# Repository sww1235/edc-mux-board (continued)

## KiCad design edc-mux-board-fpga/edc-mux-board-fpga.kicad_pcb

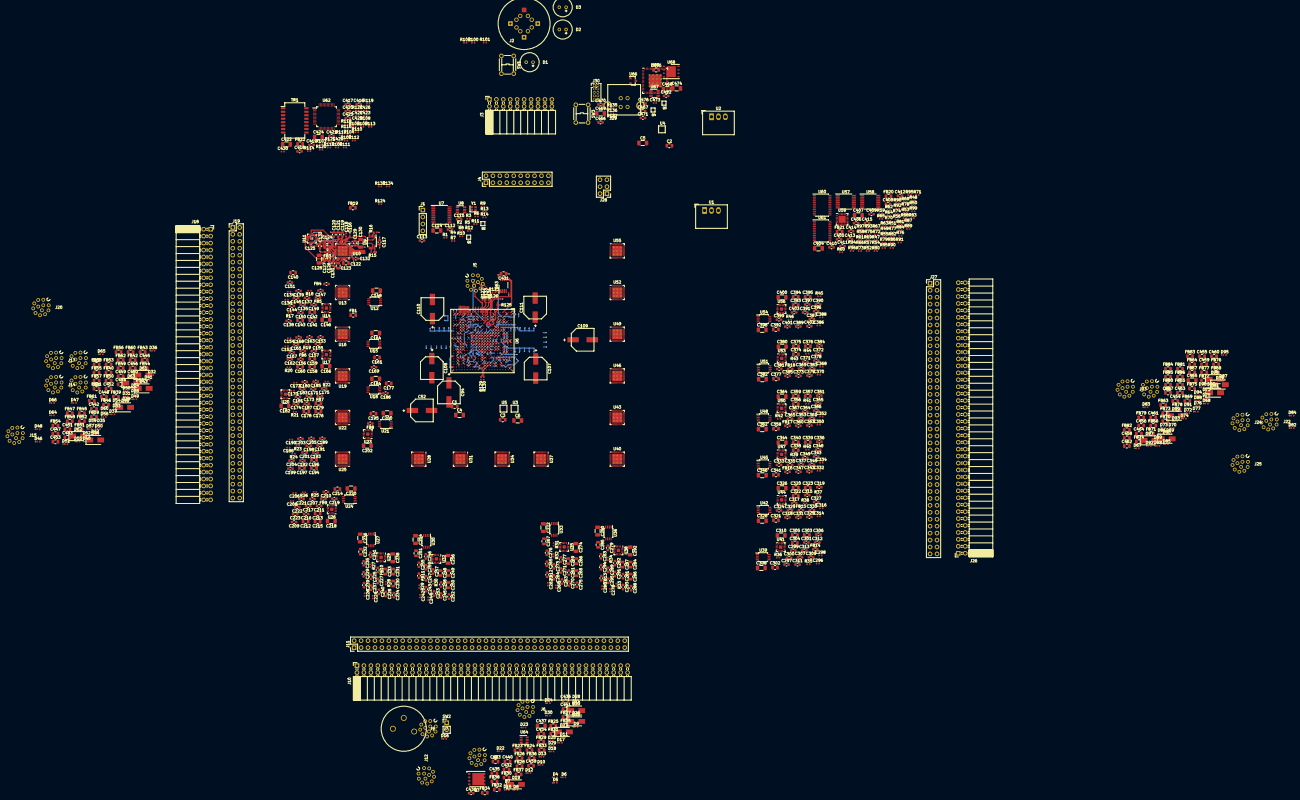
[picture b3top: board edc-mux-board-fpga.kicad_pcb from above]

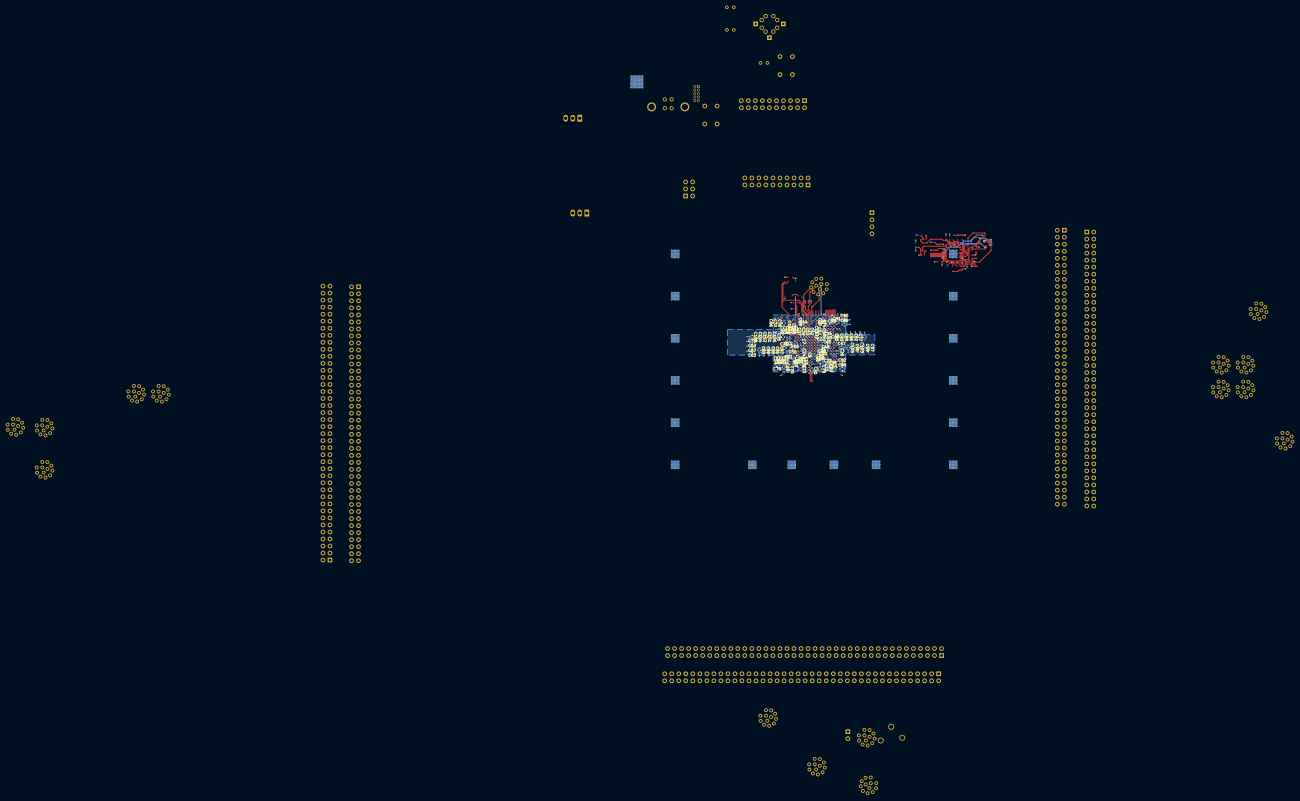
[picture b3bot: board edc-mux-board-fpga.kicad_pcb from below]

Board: 4 copper layers, 906 parts (100 on the bottom side), 887 nets.

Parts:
C1, C2, C3: 4.7uF X7R; C_0805_2012Metric
C4, C5, C6, C114, C128, C130, C146, C148, C164, C166, C182, C184, C200, C202, C218, C220, C236, C238, C254, C256, C272, C274, C290, C292, C308, C310, C326, C328, C344, C346, C362, C364, C380, C382, C398, C400, C404, C407, C422, C424, C437, C465, C468, C469, C474: 10uF X7R; C_1206_3216Metric
C7, C8, C9, C10, C11, C12, C13, C14, C15, C16, C17, C18, C19, C20, C21, C22, C23, C24, C25, C27, C28, C30, C31, C33, C36, C423, C430: 4.7nF X7R; C_0402_1005Metric
C26, C29, C32, C35, C38, C40, C43, C46, C49, C51, C54, C56, C58, C59, C61, C426: 10nF X7R; C_0402_1005Metric
C34, C37, C39, C42, C45, C48, C50, C53, C55, C57: 47nF X7R; C_0603_1608Metric
C41, C44, C60, C62, C63, C64, C65, C66, C67, C68, C69, C70, C71, C72, C73, C74, C75, C76, C77, C78, C79, C81, C112, C113, C115, C117, C119, C120, C126, C129, C131, C132, C133, C135, C137, C138, C144, C147, C149, C150, C151, C153, C155, C156, C162, C165, C167, C168, C169, C171, C173, C174, C180, C183, C185, C186, C187, C189, C191, C192, C198, C201, C203, C204, C205, C207, C209, C210, C216, C219, C221, C222, C223, C225, C227, C228, C234, C237, C239, C240, C241, C243, C245, C246, C252, C255, C257, C258, C259, C261, C263, C264, C270, C273, C275, C276, C277, C279, C281, C282, C288, C291, C293, C294, C295, C297, C299, C300, C306, C309, C311, C312, C313, C315, C317, C318, C324, C327, C329, C330, C331, C333, C335, C336, C342, C345, C347, C348, C349, C351, C353, C354, C360, C363, C365, C366, C367, C369, C371, C372, C378, C381, C383, C384, C385, C387, C389, C390, C396, C399, C401, C402, C403, C406, C409, C411, C413, C415, C416, C417, C418, C419, C420, C421, C425, C466, C470, C471, C476: 100nF X7R; C_0603_1608Metric
C47, C84, C86, C88, C90, C92, C97, C98, C99, C100, C101, C102, C103, C104, C105, C106, C121, C127, C139, C145, C157, C163, C175, C181, C193, C199, C211, C217, C229, C235, C247, C253, C265, C271, C283, C289, C301, C307, C319, C325, C337, C343, C355, C361, C373, C379, C391, C397, C405, C408, C410, C412, C414, C467, C472: 1uF X7R; C_0603_1608Metric
C52, C94, C107, C108, C109, C110, C111: 47uF; CP_ELEC_8.3x8.3x11.7mm_SMD
C80, C82, C83, C85, C87, C89, C91, C93, C95, C96, C438: 220nF X7R; C_0603_1608Metric
C116, C118, C134, C136, C152, C154, C170, C172, C188, C190, C206, C208, C224, C226, C242, C244, C260, C262, C278, C280, C296, C298, C314, C316, C332, C334, C350, C352, C368, C370, C386, C388: 33pF NP0; C_0402_1005Metric
C122, C123, C140, C141, C158, C159, C176, C177, C194, C195, C212, C213, C230, C231, C248, C249, C266, C267, C284, C285, C302, C303, C320, C321, C338, C339, C356, C357, C374, C375, C392, C393, C475: 2.2uF X7R; C_0805_2012Metric
C124, C125, C142, C143, C160, C161, C178, C179, C196, C197, C214, C215, C232, C233, C250, C251, C268, C269, C286, C287, C304, C305, C322, C323, C340, C341, C358, C359, C376, C377, C394, C395, C431, C432, C433, C434, C435, C436, C439, C440, C441, C442, C443, C444, C445, C446, C447, C448, C449, C450, C451, C452, C453, C454, C455, C456, C457, C458, C459, C460, C461, C462, C463, C464: 1uF X7R flex; C_0805_2012Metric
C427, C428: 6.8nF X7R; C_0402_1005Metric
C429: 22nF X7R; C_0402_1005Metric
C473: 100pF C0G; C_0402_1005Metric
D1: LNK_GRN; Q6-pins-epoxy
D2: PWR_RED; Q6-pins-epoxy
D3: ACT_YLW; Q6-pins-epoxy
D4, D5, D6, D7, D8, D9, D10, D11, D12, D13, D14, D15, D16, D17, D18, D22, D23, D24, D25, D26, D28, D29, D30, D31, D32, D33, D34, D35, D36, D37, D38, D39, D40, D41, D42, D46, D47, D48, D49, D50, D51, D52, D53, D54, D55, D56, D57, D58, D59, D60, D64, D65, D66, D67, D68, D69, D70, D71, D72, D73, D74, D75, D76, D77, D78, D82, D83, D84, D85, D86, D87, D88, D89, D90, D91, D92, D93, D94, D95, D96: 30pF 30kV; D_0402_1005Metric
D19, D20, D21, D27, D43, D44, D45, D61, D62, D63, D79, D80, D81, D97, D98, D99: 12V_Vrso; D_SMA
FB1, FB2, FB19, FB20, FB21, FB22, FB23, FB24, FB25, FB26, FB27, FB28, FB29, FB30, FB31, FB32, FB33, FB34, FB35, FB36, FB37, FB38, FB39, FB40, FB41, FB42, FB43, FB44, FB45, FB46, FB47, FB48, FB49, FB50, FB51, FB52, FB53, FB54, FB55, FB56, FB57, FB58, FB59, FB60, FB61, FB62, FB63, FB64, FB65, FB66, FB67, FB68, FB69, FB70, FB71, FB72, FB73, FB74, FB75, FB76, FB77, FB78, FB79, FB80, FB81, FB82, FB83, FB84, FB85, FB86: 600Ω @ 100MHz; L_0805_2012Metric
FB3, FB4, FB5, FB6, FB7, FB8, FB9, FB10, FB11, FB12, FB13, FB14, FB15, FB16, FB17, FB18: 220Ω/2A; L_0603_1608Metric
J1: OSC_PRG_HDR; PinHeader_1x04_P2.54mm_Vertical
J2: Ethernet; 43-02758
J3: Left Mezzanine Board Connector (Daughterboard); PinSocket_2x10_P2.54mm_Horizontal
J4: Left Mezzanine Board Connector (Motherboard); PinHeader_2x10_P2.54mm_Vertical
J5: Device 6; T4141012121-000
J6: Device 7; T4141012121-000
J7: Device 8; T4141012121-000
J8: Device 9; T4141012121-000
J9: Power In; PCL712AS
J10, J18, J26: Left Mezzanine Board Connector (Daughterboard); PinSocket_2x40_P2.54mm_Horizontal
J11, J19, J27: Left Mezzanine Board Connector (Motherboard); PinHeader_2x40_P2.54mm_Vertical
J12: Device 0; T4141012121-000
J13: Device 1; T4141012121-000
J14: Device 2; T4141012121-000
J15: Device 3; T4141012121-000
J16: Device 4; T4141012121-000
J17: Device 5; T4141012121-000
J20: Device 10; T4141012121-000
J21: Device 11; T4141012121-000
J22: Device 12; T4141012121-000
J23: Device 13; T4141012121-000
J24: Device 14; T4141012121-000
J25: Device 15; T4141012121-000
J28: PRG/SWD; PinHeader_2x03_P2.54mm_Vertical
J29: USB PRG; UJ2-BV-1-TH
J30: FPGA_JTAG; PinHeader_2x05_P1.27mm_Vertical
Q1, Q2, Q4, Q5: CSD22206W; DSBGA9
Q3: CSD18501Q5A; TDSON-8-1
R1, R3, R4, R5, R125, R132: 1kΩ; R_0402_1005Metric
R2, R104, R105, R106, R107: 0Ω; R_0402_1005Metric
R6, R7, R47, R48, R65, R66, R67, R68, R69, R70, R71, R72, R73, R74, R75, R76, R77, R78, R79, R80, R81, R82, R83, R84, R85, R86, R87, R88, R89, R90, R91, R92, R93, R94, R95, R96, R97, R98, R99, R123, R124, R130, R131, R133, R134, R135, R136, R137: 10kΩ; R_0402_1005Metric
R8, R128: 470kΩ; R_0402_1005Metric
R9, R10, R11, R12, R13, R14, R49, R50, R51, R52, R53, R54, R55, R56, R57, R58, R59, R60, R61, R62, R63, R64: 5Ω; R_0402_1005Metric
R15, R16, R17, R18, R19, R20, R21, R22, R23, R24, R25, R26, R27, R28, R29, R30, R31, R32, R33, R34, R35, R36, R37, R38, R39, R40, R41, R42, R43, R44, R45, R46: 750Ω; R_0402_1005Metric
R100, R101, R102, R127: 330Ω; R_0402_1005Metric
R103: 12.4Ω 1%; R_0402_1005Metric
R108, R110: 82Ω 1%; R_0402_1005Metric
R109, R111, R117, R118, R119, R120, R121, R122: 49.9Ω 1%; R_0402_1005Metric
R112: 10Ω 1%; R_0402_1005Metric
R113, R114: 75Ω 1%; R_0402_1005Metric
R115, R116: 150Ω 1%; R_0402_1005Metric
R126: 2k2Ω; R_0402_1005Metric
R129: 25Ω; R_0402_1005Metric
SW1: LED_ENABLE; TL1105
SW2: Power Switch; PinHeader_1x02_P2.54mm_Vertical
SW3: Reset (Microprocessor); TL1105
TR1: H1102NL; Transformer_Pulse_H1100NL
U1: R-78B12-2.0; Converter_DCDC_RECOM_R-78B-2.0_THT
U2: R-78B3.3-2.0; Converter_DCDC_RECOM_R-78B-2.0_THT
U3, U4: EP5358HUI; ENPIRION_QFN16_2.5x2.25x1.1mm-0.4mm
U5: EP5358LUI; ENPIRION_QFN16_2.5x2.25x1.1mm-0.4mm
U6: 10CL040YF484I7G; FBGA-484_23.0x23.0mm_Layout22x22_P1.0mm
U7: CDCE706; TSSOP-20_4.4x6.5mm_P0.65mm
U8, U67: LTC4412; TSOT-23-6
U9, U12, U15, U18, U21, U24, U27, U30, U33, U36, U39, U42, U45, U48, U51, U54: P82B96; TSSOP-8_3x3mm_P0.65mm
U10, U13, U16, U19, U22, U25, U28, U31, U34, U37, U40, U43, U46, U49, U52, U55: TLV320AIC3206; UQFN-40-1EP_5x5mm_P0.4mm_EP3.8x3.8mm_ThermalVias
U11, U14, U17, U20, U23, U26, U29, U32, U35, U38, U41, U44, U47, U50, U53, U56: MAX4910; TQFN-16-1EP_3x3mm_P0.5mm_EP1.23x1.23mm
U57, U58: CDCLVC1108; TSSOP-16_4.4x5mm_P0.65mm
U59: TCA9555RTWR; QFN-24-1EP_4x4mm_P0.5mm_EP2.6x2.6mm
U60, U61: TCA9548A; TSSOP-24_4.4x7.8mm_P0.65mm
U62: W5500; TQFP-48_7x7mm_P0.5mm
U63: LM74610-Q1; VSSOP-8_3.0x3.0mm_P0.65mm
U64: TPD3S014; SOT-23-6
U65: SAMD21JXXAM; QFN-64-1EP_9x9mm_P0.5mm_EP4.7x4.7mm_ThermalVias
U66: MCP1812; SOT-23
U68: S25FL128L; WSON-8-1EP_6x5mm_P1.27mm_EP3.4x4mm
Y1: SiT1602BI-71-33E-48.000000; Crystal_SMD_2016-4Pin_2.0x1.6mm

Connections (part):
+1V2: C6.1, C7.1, C8.1, C9.1, C12.1, C15.1, C18.1, C21.1, C24.1, C27.1, C30.1, C34.1, C37.1, C39.1, C42.1, C45.1, C48.1, C50.1, C53.1, C55.1, C57.1, C60.1, C62.1, C63.1, C65.1, C67.1, C69.1, C71.1, C73.1, C75.1, C77.1, C80.1, C82.1, C83.1, C85.1, C87.1, C89.1, C91.1, C93.1, C95.1, C96.1, C97.1, C98.1, C99.1, C100.1, C101.1, C102.1, C103.1, C104.1, C105.1, C106.1, C107.1, C108.1, C109.1, C110.1, C111.1, FB1.1, U5.5, U5.7, U5.8, U6.G12, U6.H9, U6.J10, U6.J11, U6.J12, U6.J13, U6.J14, U6.J16, U6.K9, U6.K14, U6.K15, U6.L9, U6.L14, U6.L16, U6.M9, U6.M14, U6.M15, U6.N9, U6.N14, U6.P9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
+1V8: C5.1, C126.2, C127.2, C128.2, C131.2, C132.2, C144.2, C145.2, C146.2, C149.2, C150.2, C162.2, C163.2, C164.2, C167.2, C168.2, C180.2, C181.2, C182.2, C185.2, C186.2, C198.2, C199.2, C200.2, C203.2, C204.2, C216.2, C217.2, C218.2, C221.2, C222.2, C234.2, C235.2, C236.2, C239.2, C240.2, C252.2, C253.2, C254.2, C257.2, C258.2, C270.2, C271.2, C272.2, C275.2, C276.2, C288.2, C289.2, C290.2, C293.2, C294.2, C306.2, C307.2, C308.2, C311.2, C312.2, C324.2, C325.2, C326.2, C329.2, C330.2, C342.2, C343.2, C344.2, C347.2, C348.2, C360.2, C361.2, C362.2, C365.2, C366.2, C378.2, C379.2, C380.2, C383.2, C384.2, C396.2, C397.2, C398.2, C401.2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
+2V5: C4.1, C10.1, C13.1, C16.1, C19.1, C22.1, C25.1, C28.1, C31.1, C33.1, C36.1, C40.1, C43.1, C46.1, C49.1, C51.1, C54.1, C56.1, C58.1, C59.1, C61.1, C64.1, C66.1, C68.1, C70.1, C72.1, C74.1, C76.1, C78.1, C79.1, C81.1, C84.1, C86.1, C88.1, C90.1, C92.1, C94.1, J30.9, R136.2, R137.2, U3.5, U3.7, U3.8, U6.F18, U6.G6, U6.T6, U6.U18
+3V3: C1.1, C2.1, C3.1, C11.1, C14.1, C17.1, C20.1, C23.1, C26.1, C29.1, C32.1, C35.1, C38.1, C41.1, C44.1, C47.1, C52.1, C129.2, C130.1, C133.2, C147.2, C148.1, C151.2, C165.2, C166.1, C169.2, C183.2, C184.1, C187.2, C201.2, C202.1, C205.2, C219.2, C220.1, C223.2, C237.2, C238.1, C241.2, C255.2, C256.1, C259.2, C273.2, C274.1, C277.2, C291.2, C292.1, C295.2, C309.2, C310.1, C313.2, C327.2, C328.1, C331.2, C345.2, C346.1, C349.2, C363.2, C364.1, C367.2, C381.2, C382.1, C385.2, C399.2, C400.1, C403.2, C404.1, C407.1, C410.1, C411.2, C412.1, C413.2, C414.1, C415.2, C424.2, C425.2, C473.2, C476.2, FB19.2, FB20.2, FB21.2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
+12P: J11.27, J11.28, J11.29, J11.30, J11.31, J11.32, J11.49, J11.50, J11.51, J11.52, J11.53, J11.54, U1.1
+12V: C117.1, C135.1, C153.1, C171.1, C189.1, C207.1, C225.1, C243.1, C261.1, C279.1, C297.1, C315.1, C333.1, C351.1, C369.1, C387.1, J11.37, J11.38, J11.39, J11.40, J11.41, J11.42, J11.43, J11.44, J19.37, J19.38, J19.39, J19.40, J19.41, J19.42, J19.43, J19.44, J27.37, J27.38, J27.39, J27.40, J27.41, J27.42, J27.43, J27.44, R15.1, R16.1, R17.1, R18.1, R19.1, R20.1, R21.1, R22.1, R23.1, R24.1, R25.1, R26.1, R27.1, R28.1, R29.1, R30.1, R31.1, R32.1, R33.1, R34.1, R35.1, R36.1, R37.1, R38.1, R39.1, R40.1, R41.1, R42.1, R43.1, R44.1, R45.1, R46.1, U1.3, U2.1, U9.8, U12.8, U15.8, U18.8, U21.8, U24.8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
/ATTACH_INT: U6.R1, U65.40
/Bottom Side Daughterboard Connector Interconnects/AUD_GND6: J11.5, U29.4
/Bottom Side Daughterboard Connector Interconnects/AUD_GND7: J11.17, U32.4
/Bottom Side Daughterboard Connector Interconnects/AUD_GND8: J11.63, U35.4
/Bottom Side Daughterboard Connector Interconnects/AUD_GND9: J11.75, U38.4
/Bottom Side Daughterboard Connector Interconnects/L_IN6: C224.2, J11.3, U28.17
/Bottom Side Daughterboard Connector Interconnects/L_IN7: C242.2, J11.15, U31.17
/Bottom Side Daughterboard Connector Interconnects/L_IN8: C260.2, J11.61, U34.17
/Bottom Side Daughterboard Connector Interconnects/L_IN9: C278.2, J11.73, U37.17
/Bottom Side Daughterboard Connector Interconnects/L_OUT6: J11.4, U29.8
/Bottom Side Daughterboard Connector Interconnects/L_OUT7: J11.16, U32.8
/Bottom Side Daughterboard Connector Interconnects/L_OUT8: J11.62, U35.8
/Bottom Side Daughterboard Connector Interconnects/L_OUT9: J11.74, U38.8
/Bottom Side Daughterboard Connector Interconnects/M_+12V: D19.1, D20.1, D21.1, D27.1, J5.12, J6.12, J7.12, J8.12, J10.37, J10.38, J10.39, J10.40, J10.41, J10.42, J10.43, J10.44
/Bottom Side Daughterboard Connector Interconnects/M_AUD_GND6: J5.1, J10.5
/Bottom Side Daughterboard Connector Interconnects/M_AUD_GND7: J6.1, J10.17
/Bottom Side Daughterboard Connector Interconnects/M_AUD_GND8: J7.1, J10.63
/Bottom Side Daughterboard Connector Interconnects/M_AUD_GND9: J8.1, J10.75
/Bottom Side Daughterboard Connector Interconnects/M_GND: C437.1, D4.2, D5.2, D6.2, D7.2, D8.2, D9.2, D10.2, D11.2, D12.2, D13.2, D14.2, D15.2, D16.2, D17.2, D18.2, D19.2, D20.2, D21.2, D22.2, D23.2, D24.2, D25.2, D26.2, D27.2, J5.6, J5.10, J6.6, J6.10, J7.6, J7.10, J8.6, J8.10, J9.2, J9.3, J10.6, J10.11, J10.12, J10.18, J10.23, J10.24, J10.25, J10.26, J10.33, J10.34, J10.35, J10.36, J10.45, J10.46, J10.47, J10.48, J10.55, J10.56, J10.57, J10.58, J10.64, J10.69, J10.70, J10.76
/Bottom Side Daughterboard Connector Interconnects/M_ID_PIN6: D16.1, J5.11, J10.9
/Bottom Side Daughterboard Connector Interconnects/M_ID_PIN7: D17.1, J6.11, J10.21
/Bottom Side Daughterboard Connector Interconnects/M_ID_PIN8: D18.1, J7.11, J10.67
/Bottom Side Daughterboard Connector Interconnects/M_ID_PIN9: D26.1, J8.11, J10.79
/Bottom Side Daughterboard Connector Interconnects/M_INT_6: J5.9, J10.7
/Bottom Side Daughterboard Connector Interconnects/M_INT_7: J6.9, J10.19
/Bottom Side Daughterboard Connector Interconnects/M_INT_8: J7.9, J10.65
/Bottom Side Daughterboard Connector Interconnects/M_INT_9: J8.9, J10.77
/Bottom Side Daughterboard Connector Interconnects/M_L_IN6: C431.1, J10.3
/Bottom Side Daughterboard Connector Interconnects/M_L_IN7: C432.1, J10.15
/Bottom Side Daughterboard Connector Interconnects/M_L_IN8: C433.1, J10.61
/Bottom Side Daughterboard Connector Interconnects/M_L_IN9: C439.1, J10.73
/Bottom Side Daughterboard Connector Interconnects/M_L_OUT6: FB28.1, J10.2
/Bottom Side Daughterboard Connector Interconnects/M_L_OUT7: FB29.1, J10.16
/Bottom Side Daughterboard Connector Interconnects/M_L_OUT8: FB30.1, J10.62
/Bottom Side Daughterboard Connector Interconnects/M_L_OUT9: FB36.1, J10.74
/Bottom Side Daughterboard Connector Interconnects/M_PWR_IN: J10.27, J10.28, J10.29, J10.30, J10.31, J10.32, J10.49, J10.50, J10.51, J10.52, J10.53, J10.54, Q3.5, U63.8
/Bottom Side Daughterboard Connector Interconnects/M_R_IN6: C434.1, J10.1
/Bottom Side Daughterboard Connector Interconnects/M_R_IN7: C435.1, J10.13
/Bottom Side Daughterboard Connector Interconnects/M_R_IN8: C436.1, J10.59
/Bottom Side Daughterboard Connector Interconnects/M_R_IN9: C440.1, J10.71
/Bottom Side Daughterboard Connector Interconnects/M_R_OUT6: FB31.1, J10.4
/Bottom Side Daughterboard Connector Interconnects/M_R_OUT7: FB32.1, J10.14
/Bottom Side Daughterboard Connector Interconnects/M_R_OUT8: FB33.1, J10.60
/Bottom Side Daughterboard Connector Interconnects/M_R_OUT9: FB37.1, J10.72
/Bottom Side Daughterboard Connector Interconnects/M_SCL_HV6: J5.8, J10.8
/Bottom Side Daughterboard Connector Interconnects/M_SCL_HV7: J6.8, J10.20
/Bottom Side Daughterboard Connector Interconnects/M_SCL_HV8: J7.8, J10.66
/Bottom Side Daughterboard Connector Interconnects/M_SCL_HV9: J8.8, J10.78
/Bottom Side Daughterboard Connector Interconnects/M_SDA_HV6: J5.7, J10.10
/Bottom Side Daughterboard Connector Interconnects/M_SDA_HV7: J6.7, J10.22
/Bottom Side Daughterboard Connector Interconnects/M_SDA_HV8: J7.7, J10.68
/Bottom Side Daughterboard Connector Interconnects/M_SDA_HV9: J8.7, J10.80
/Bottom Side Daughterboard Connector Interconnects/R_IN6: C226.2, J11.1, U28.18
/Bottom Side Daughterboard Connector Interconnects/R_IN7: C244.2, J11.13, U31.18
/Bottom Side Daughterboard Connector Interconnects/R_IN8: C262.2, J11.59, U34.18
/Bottom Side Daughterboard Connector Interconnects/R_IN9: C280.2, J11.71, U37.18
/Bottom Side Daughterboard Connector Interconnects/SCL_HV6: J11.8, R27.2, U27.5, U27.6
/Bottom Side Daughterboard Connector Interconnects/SCL_HV7: J11.20, R29.2, U30.5, U30.6
/Bottom Side Daughterboard Connector Interconnects/SCL_HV8: J11.66, R31.2, U33.5, U33.6
/Bottom Side Daughterboard Connector Interconnects/SCL_HV9: J11.78, R33.2, U36.5, U36.6
/Bottom Side Daughterboard Connector Interconnects/SDA_HV6: J11.10, R28.2, U27.2, U27.3
/Bottom Side Daughterboard Connector Interconnects/SDA_HV7: J11.22, R30.2, U30.2, U30.3
/Bottom Side Daughterboard Connector Interconnects/SDA_HV8: J11.68, R32.2, U33.2, U33.3
/Bottom Side Daughterboard Connector Interconnects/SDA_HV9: J11.80, R34.2, U36.2, U36.3
/CODEC interconnection sheet/AUD_GND0: J19.5, U11.4
/CODEC interconnection sheet/AUD_GND1: J19.17, U14.4
/CODEC interconnection sheet/AUD_GND2: J19.29, U17.4
/CODEC interconnection sheet/AUD_GND3: J19.51, U20.4
/CODEC interconnection sheet/AUD_GND4: J19.63, U23.4
/CODEC interconnection sheet/AUD_GND5: J19.75, U26.4
/CODEC interconnection sheet/AUD_GND10: J27.5, U41.4
/CODEC interconnection sheet/AUD_GND11: J27.17, U44.4
/CODEC interconnection sheet/AUD_GND12: J27.29, U47.4
/CODEC interconnection sheet/AUD_GND13: J27.51, U50.4
/CODEC interconnection sheet/AUD_GND14: J27.63, U53.4
/CODEC interconnection sheet/AUD_GND15: J27.75, U56.4
/CODEC interconnection sheet/BCLK0: U6.AA4, U10.6
/CODEC interconnection sheet/BCLK1: U6.AA8, U13.6
/CODEC interconnection sheet/BCLK2: U6.AA10, U16.6
/CODEC interconnection sheet/BCLK3: U6.AA14, U19.6
/CODEC interconnection sheet/BCLK4: U6.AA16, U22.6
/CODEC interconnection sheet/BCLK5: U6.AA19, U25.6
/CODEC interconnection sheet/BCLK6: U6.Y21, U28.6
/CODEC interconnection sheet/BCLK7: U6.U21, U31.6
/CODEC interconnection sheet/BCLK8: U6.G21, U34.6
/CODEC interconnection sheet/BCLK9: U6.D21, U37.6
/CODEC interconnection sheet/BCLK10: U6.B15, U40.6
/CODEC interconnection sheet/BCLK11: U6.B13, U43.6
/CODEC interconnection sheet/BCLK12: U6.B9, U46.6
/CODEC interconnection sheet/BCLK13: U6.B7, U49.6
/CODEC interconnection sheet/BCLK14: U6.B5, U52.6
/CODEC interconnection sheet/BCLK15: U6.B3, U55.6
/CODEC interconnection sheet/DIN0: U6.AA3, U10.8
/CODEC interconnection sheet/DIN1: U6.AA7, U13.8
/CODEC interconnection sheet/DIN2: U6.AA9, U16.8
/CODEC interconnection sheet/DIN3: U6.AA13, U19.8
/CODEC interconnection sheet/DIN4: U6.AA15, U22.8
/CODEC interconnection sheet/DIN5: U6.AA18, U25.8
/CODEC interconnection sheet/DIN6: U6.AA21, U28.8
/CODEC interconnection sheet/DIN7: U6.V21, U31.8
/CODEC interconnection sheet/DIN8: U6.H21, U34.8
/CODEC interconnection sheet/DIN9: U6.E21, U37.8
/CODEC interconnection sheet/DIN10: U6.B16, U40.8
/CODEC interconnection sheet/DIN11: U6.B14, U43.8
/CODEC interconnection sheet/DIN12: U6.B10, U46.8
/CODEC interconnection sheet/DIN13: U6.B8, U49.8
/CODEC interconnection sheet/DIN14: U6.B6, U52.8
/CODEC interconnection sheet/DIN15: U6.B4, U55.8
/CODEC interconnection sheet/DOUT0: U6.AB3, U10.9
/CODEC interconnection sheet/DOUT1: U6.AB7, U13.9
/CODEC interconnection sheet/DOUT2: U6.AB9, U16.9
/CODEC interconnection sheet/DOUT3: U6.AB13, U19.9
/CODEC interconnection sheet/DOUT4: U6.AB15, U22.9
/CODEC interconnection sheet/DOUT5: U6.AB18, U25.9
/CODEC interconnection sheet/DOUT6: U6.AA22, U28.9
/CODEC interconnection sheet/DOUT7: U6.V22, U31.9
/CODEC interconnection sheet/DOUT8: U6.H22, U34.9
/CODEC interconnection sheet/DOUT9: U6.E22, U37.9
/CODEC interconnection sheet/DOUT10: U6.A16, U40.9
/CODEC interconnection sheet/DOUT11: U6.A14, U43.9
/CODEC interconnection sheet/DOUT12: U6.A10, U46.9
/CODEC interconnection sheet/DOUT13: U6.A8, U49.9
/CODEC interconnection sheet/DOUT14: U6.A6, U52.9
/CODEC interconnection sheet/DOUT15: U6.A4, U55.9
/CODEC interconnection sheet/Interface - Connector 0/GND_SENSE: FB3.1, U10.28, U11.3
/CODEC interconnection sheet/Interface - Connector 0/HPL: U10.31, U11.15
/CODEC interconnection sheet/Interface - Connector 0/HPR: U10.33, U11.7
/CODEC interconnection sheet/Interface - Connector 0/HP_~LINE~_SEL: U10.4, U11.2, U11.10
/CODEC interconnection sheet/Interface - Connector 0/LINE_OUT_L: C124.1, U11.1
/CODEC interconnection sheet/Interface - Connector 0/LINE_OUT_R: C125.1, U11.9
/CODEC interconnection sheet/Interface - Connector 0/REF: C121.2, U10.22
/CODEC interconnection sheet/Interface - Connector 0/VNEG: C123.2, U10.35
/CODEC interconnection sheet/Interface - Connector 1/GND_SENSE: FB4.1, U13.28, U14.3
/CODEC interconnection sheet/Interface - Connector 1/HPL: U13.31, U14.15
/CODEC interconnection sheet/Interface - Connector 1/HPR: U13.33, U14.7
/CODEC interconnection sheet/Interface - Connector 1/HP_~LINE~_SEL: U13.4, U14.2, U14.10
/CODEC interconnection sheet/Interface - Connector 1/LINE_OUT_L: C142.1, U14.1
/CODEC interconnection sheet/Interface - Connector 1/LINE_OUT_R: C143.1, U14.9
/CODEC interconnection sheet/Interface - Connector 1/REF: C139.2, U13.22
/CODEC interconnection sheet/Interface - Connector 1/VNEG: C141.2, U13.35
/CODEC interconnection sheet/Interface - Connector 2/GND_SENSE: FB5.1, U16.28, U17.3
/CODEC interconnection sheet/Interface - Connector 2/HPL: U16.31, U17.15
/CODEC interconnection sheet/Interface - Connector 2/HPR: U16.33, U17.7
/CODEC interconnection sheet/Interface - Connector 2/HP_~LINE~_SEL: U16.4, U17.2, U17.10
/CODEC interconnection sheet/Interface - Connector 2/LINE_OUT_L: C160.1, U17.1
/CODEC interconnection sheet/Interface - Connector 2/LINE_OUT_R: C161.1, U17.9
/CODEC interconnection sheet/Interface - Connector 2/REF: C157.2, U16.22
/CODEC interconnection sheet/Interface - Connector 2/VNEG: C159.2, U16.35
/CODEC interconnection sheet/Interface - Connector 3/GND_SENSE: FB6.1, U19.28, U20.3
/CODEC interconnection sheet/Interface - Connector 3/HPL: U19.31, U20.15
/CODEC interconnection sheet/Interface - Connector 3/HPR: U19.33, U20.7
/CODEC interconnection sheet/Interface - Connector 3/HP_~LINE~_SEL: U19.4, U20.2, U20.10
/CODEC interconnection sheet/Interface - Connector 3/LINE_OUT_L: C178.1, U20.1
/CODEC interconnection sheet/Interface - Connector 3/LINE_OUT_R: C179.1, U20.9
/CODEC interconnection sheet/Interface - Connector 3/REF: C175.2, U19.22
/CODEC interconnection sheet/Interface - Connector 3/VNEG: C177.2, U19.35
/CODEC interconnection sheet/Interface - Connector 4/GND_SENSE: FB7.1, U22.28, U23.3
/CODEC interconnection sheet/Interface - Connector 4/HPL: U22.31, U23.15
/CODEC interconnection sheet/Interface - Connector 4/HPR: U22.33, U23.7
/CODEC interconnection sheet/Interface - Connector 4/HP_~LINE~_SEL: U22.4, U23.2, U23.10
/CODEC interconnection sheet/Interface - Connector 4/LINE_OUT_L: C196.1, U23.1
/CODEC interconnection sheet/Interface - Connector 4/LINE_OUT_R: C197.1, U23.9
/CODEC interconnection sheet/Interface - Connector 4/REF: C193.2, U22.22
/CODEC interconnection sheet/Interface - Connector 4/VNEG: C195.2, U22.35
/CODEC interconnection sheet/Interface - Connector 5/GND_SENSE: FB8.1, U25.28, U26.3
/CODEC interconnection sheet/Interface - Connector 5/HPL: U25.31, U26.15
/CODEC interconnection sheet/Interface - Connector 5/HPR: U25.33, U26.7
/CODEC interconnection sheet/Interface - Connector 5/HP_~LINE~_SEL: U25.4, U26.2, U26.10
/CODEC interconnection sheet/Interface - Connector 5/LINE_OUT_L: C214.1, U26.1
/CODEC interconnection sheet/Interface - Connector 5/LINE_OUT_R: C215.1, U26.9
/CODEC interconnection sheet/Interface - Connector 5/REF: C211.2, U25.22
/CODEC interconnection sheet/Interface - Connector 5/VNEG: C213.2, U25.35
/CODEC interconnection sheet/Interface - Connector 6/GND_SENSE: FB9.1, U28.28, U29.3
/CODEC interconnection sheet/Interface - Connector 6/HPL: U28.31, U29.15
/CODEC interconnection sheet/Interface - Connector 6/HPR: U28.33, U29.7
/CODEC interconnection sheet/Interface - Connector 6/HP_~LINE~_SEL: U28.4, U29.2, U29.10
/CODEC interconnection sheet/Interface - Connector 6/LINE_OUT_L: C232.1, U29.1
/CODEC interconnection sheet/Interface - Connector 6/LINE_OUT_R: C233.1, U29.9
/CODEC interconnection sheet/Interface - Connector 6/REF: C229.2, U28.22
/CODEC interconnection sheet/Interface - Connector 6/VNEG: C231.2, U28.35
/CODEC interconnection sheet/Interface - Connector 7/GND_SENSE: FB10.1, U31.28, U32.3
/CODEC interconnection sheet/Interface - Connector 7/HPL: U31.31, U32.15
/CODEC interconnection sheet/Interface - Connector 7/HPR: U31.33, U32.7
/CODEC interconnection sheet/Interface - Connector 7/HP_~LINE~_SEL: U31.4, U32.2, U32.10
/CODEC interconnection sheet/Interface - Connector 7/LINE_OUT_L: C250.1, U32.1
/CODEC interconnection sheet/Interface - Connector 7/LINE_OUT_R: C251.1, U32.9
/CODEC interconnection sheet/Interface - Connector 7/REF: C247.2, U31.22
/CODEC interconnection sheet/Interface - Connector 7/VNEG: C249.2, U31.35
/CODEC interconnection sheet/Interface - Connector 8/GND_SENSE: FB11.1, U34.28, U35.3
/CODEC interconnection sheet/Interface - Connector 8/HPL: U34.31, U35.15
/CODEC interconnection sheet/Interface - Connector 8/HPR: U34.33, U35.7
/CODEC interconnection sheet/Interface - Connector 8/HP_~LINE~_SEL: U34.4, U35.2, U35.10
/CODEC interconnection sheet/Interface - Connector 8/LINE_OUT_L: C268.1, U35.1
/CODEC interconnection sheet/Interface - Connector 8/LINE_OUT_R: C269.1, U35.9
/CODEC interconnection sheet/Interface - Connector 8/REF: C265.2, U34.22
/CODEC interconnection sheet/Interface - Connector 8/VNEG: C267.2, U34.35
/CODEC interconnection sheet/Interface - Connector 9/GND_SENSE: FB12.1, U37.28, U38.3
/CODEC interconnection sheet/Interface - Connector 9/HPL: U37.31, U38.15
/CODEC interconnection sheet/Interface - Connector 9/HPR: U37.33, U38.7
/CODEC interconnection sheet/Interface - Connector 9/HP_~LINE~_SEL: U37.4, U38.2, U38.10
/CODEC interconnection sheet/Interface - Connector 9/LINE_OUT_L: C286.1, U38.1
/CODEC interconnection sheet/Interface - Connector 9/LINE_OUT_R: C287.1, U38.9
/CODEC interconnection sheet/Interface - Connector 9/REF: C283.2, U37.22
/CODEC interconnection sheet/Interface - Connector 9/VNEG: C285.2, U37.35
/CODEC interconnection sheet/Interface - Connector 10/GND_SENSE: FB13.1, U40.28, U41.3
/CODEC interconnection sheet/Interface - Connector 10/HPL: U40.31, U41.15
/CODEC interconnection sheet/Interface - Connector 10/HPR: U40.33, U41.7
/CODEC interconnection sheet/Interface - Connector 10/HP_~LINE~_SEL: U40.4, U41.2, U41.10
/CODEC interconnection sheet/Interface - Connector 10/LINE_OUT_L: C304.1, U41.1
/CODEC interconnection sheet/Interface - Connector 10/LINE_OUT_R: C305.1, U41.9
/CODEC interconnection sheet/Interface - Connector 10/REF: C301.2, U40.22
/CODEC interconnection sheet/Interface - Connector 10/VNEG: C303.2, U40.35
/CODEC interconnection sheet/Interface - Connector 11/GND_SENSE: FB14.1, U43.28, U44.3
/CODEC interconnection sheet/Interface - Connector 11/HPL: U43.31, U44.15
/CODEC interconnection sheet/Interface - Connector 11/HPR: U43.33, U44.7
/CODEC interconnection sheet/Interface - Connector 11/HP_~LINE~_SEL: U43.4, U44.2, U44.10
/CODEC interconnection sheet/Interface - Connector 11/LINE_OUT_L: C322.1, U44.1
/CODEC interconnection sheet/Interface - Connector 11/LINE_OUT_R: C323.1, U44.9
/CODEC interconnection sheet/Interface - Connector 11/REF: C319.2, U43.22
/CODEC interconnection sheet/Interface - Connector 11/VNEG: C321.2, U43.35
/CODEC interconnection sheet/Interface - Connector 12/GND_SENSE: FB15.1, U46.28, U47.3
/CODEC interconnection sheet/Interface - Connector 12/HPL: U46.31, U47.15
/CODEC interconnection sheet/Interface - Connector 12/HPR: U46.33, U47.7
/CODEC interconnection sheet/Interface - Connector 12/HP_~LINE~_SEL: U46.4, U47.2, U47.10
/CODEC interconnection sheet/Interface - Connector 12/LINE_OUT_L: C340.1, U47.1
/CODEC interconnection sheet/Interface - Connector 12/LINE_OUT_R: C341.1, U47.9
/CODEC interconnection sheet/Interface - Connector 12/REF: C337.2, U46.22
/CODEC interconnection sheet/Interface - Connector 12/VNEG: C339.2, U46.35
/CODEC interconnection sheet/Interface - Connector 13/GND_SENSE: FB16.1, U49.28, U50.3
/CODEC interconnection sheet/Interface - Connector 13/HPL: U49.31, U50.15
/CODEC interconnection sheet/Interface - Connector 13/HPR: U49.33, U50.7
/CODEC interconnection sheet/Interface - Connector 13/HP_~LINE~_SEL: U49.4, U50.2, U50.10
/CODEC interconnection sheet/Interface - Connector 13/LINE_OUT_L: C358.1, U50.1
/CODEC interconnection sheet/Interface - Connector 13/LINE_OUT_R: C359.1, U50.9
/CODEC interconnection sheet/Interface - Connector 13/REF: C355.2, U49.22
/CODEC interconnection sheet/Interface - Connector 13/VNEG: C357.2, U49.35
/CODEC interconnection sheet/Interface - Connector 14/GND_SENSE: FB17.1, U52.28, U53.3
/CODEC interconnection sheet/Interface - Connector 14/HPL: U52.31, U53.15
/CODEC interconnection sheet/Interface - Connector 14/HPR: U52.33, U53.7
/CODEC interconnection sheet/Interface - Connector 14/HP_~LINE~_SEL: U52.4, U53.2, U53.10
/CODEC interconnection sheet/Interface - Connector 14/LINE_OUT_L: C376.1, U53.1
/CODEC interconnection sheet/Interface - Connector 14/LINE_OUT_R: C377.1, U53.9
/CODEC interconnection sheet/Interface - Connector 14/REF: C373.2, U52.22
/CODEC interconnection sheet/Interface - Connector 14/VNEG: C375.2, U52.35
/CODEC interconnection sheet/Interface - Connector 15/GND_SENSE: FB18.1, U55.28, U56.3
/CODEC interconnection sheet/Interface - Connector 15/HPL: U55.31, U56.15
/CODEC interconnection sheet/Interface - Connector 15/HPR: U55.33, U56.7
/CODEC interconnection sheet/Interface - Connector 15/HP_~LINE~_SEL: U55.4, U56.2, U56.10
/CODEC interconnection sheet/Interface - Connector 15/LINE_OUT_L: C394.1, U56.1
/CODEC interconnection sheet/Interface - Connector 15/LINE_OUT_R: C395.1, U56.9
/CODEC interconnection sheet/Interface - Connector 15/REF: C391.2, U55.22
/CODEC interconnection sheet/Interface - Connector 15/VNEG: C393.2, U55.35
/CODEC interconnection sheet/L_IN0: C116.2, J19.3, U10.17
/CODEC interconnection sheet/L_IN1: C134.2, J19.15, U13.17
/CODEC interconnection sheet/L_IN2: C152.2, J19.27, U16.17
/CODEC interconnection sheet/L_IN3: C170.2, J19.49, U19.17
/CODEC interconnection sheet/L_IN4: C188.2, J19.61, U22.17
/CODEC interconnection sheet/L_IN5: C206.2, J19.73, U25.17
/CODEC interconnection sheet/L_IN10: C296.2, J27.3, U40.17
/CODEC interconnection sheet/L_IN11: C314.2, J27.15, U43.17
/CODEC interconnection sheet/L_IN12: C332.2, J27.27, U46.17
/CODEC interconnection sheet/L_IN13: C350.2, J27.49, U49.17
/CODEC interconnection sheet/L_IN14: C368.2, J27.61, U52.17
/CODEC interconnection sheet/L_IN15: C386.2, J27.73, U55.17
/CODEC interconnection sheet/L_OUT0: J19.4, U11.16
/CODEC interconnection sheet/L_OUT1: J19.16, U14.16
/CODEC interconnection sheet/L_OUT2: J19.28, U17.16
/CODEC interconnection sheet/L_OUT3: J19.50, U20.16
/CODEC interconnection sheet/L_OUT4: J19.62, U23.16
/CODEC interconnection sheet/L_OUT5: J19.74, U26.16
/CODEC interconnection sheet/L_OUT6: J11.2, U29.16
/CODEC interconnection sheet/L_OUT7: J11.14, U32.16
/CODEC interconnection sheet/L_OUT8: J11.60, U35.16
/CODEC interconnection sheet/L_OUT9: J11.72, U38.16
/CODEC interconnection sheet/L_OUT10: J27.4, U41.16
/CODEC interconnection sheet/L_OUT11: J27.16, U44.16
/CODEC interconnection sheet/L_OUT12: J27.28, U47.16
/CODEC interconnection sheet/L_OUT13: J27.50, U50.16
/CODEC interconnection sheet/L_OUT14: J27.62, U53.16
/CODEC interconnection sheet/L_OUT15: J27.74, U56.16
/CODEC interconnection sheet/MCLK0: R49.1, U10.5
/CODEC interconnection sheet/MCLK1: R50.1, U13.5
/CODEC interconnection sheet/MCLK2: R51.1, U16.5
/CODEC interconnection sheet/MCLK3: R52.1, U19.5
/CODEC interconnection sheet/MCLK4: R53.1, U22.5
/CODEC interconnection sheet/MCLK5: R54.1, U25.5
/CODEC interconnection sheet/MCLK6: R55.1, U28.5
/CODEC interconnection sheet/MCLK7: R56.1, U31.5
/CODEC interconnection sheet/MCLK8: R57.1, U34.5
/CODEC interconnection sheet/MCLK9: R58.1, U37.5
/CODEC interconnection sheet/MCLK10: R59.1, U40.5
/CODEC interconnection sheet/MCLK11: R60.1, U43.5
/CODEC interconnection sheet/MCLK12: R61.1, U46.5
/CODEC interconnection sheet/MCLK13: R62.1, U49.5
/CODEC interconnection sheet/MCLK14: R63.1, U52.5
/CODEC interconnection sheet/MCLK15: R64.1, U55.5
/CODEC interconnection sheet/R_IN0: C118.2, J19.1, U10.18
/CODEC interconnection sheet/R_IN1: C136.2, J19.13, U13.18
/CODEC interconnection sheet/R_IN2: C154.2, J19.25, U16.18
/CODEC interconnection sheet/R_IN3: C172.2, J19.47, U19.18
/CODEC interconnection sheet/R_IN4: C190.2, J19.59, U22.18
/CODEC interconnection sheet/R_IN5: C208.2, J19.71, U25.18
/CODEC interconnection sheet/R_IN10: C298.2, J27.1, U40.18
/CODEC interconnection sheet/R_IN11: C316.2, J27.13, U43.18
/CODEC interconnection sheet/R_IN12: C334.2, J27.25, U46.18
/CODEC interconnection sheet/R_IN13: C352.2, J27.47, U49.18
/CODEC interconnection sheet/R_IN14: C370.2, J27.59, U52.18
/CODEC interconnection sheet/R_IN15: C388.2, J27.71, U55.18
/CODEC interconnection sheet/R_OUT0: J19.2, U11.8
/CODEC interconnection sheet/R_OUT1: J19.14, U14.8
/CODEC interconnection sheet/R_OUT2: J19.26, U17.8
/CODEC interconnection sheet/R_OUT3: J19.48, U20.8
/CODEC interconnection sheet/R_OUT4: J19.60, U23.8
/CODEC interconnection sheet/R_OUT5: J19.72, U26.8
/CODEC interconnection sheet/R_OUT10: J27.2, U41.8
/CODEC interconnection sheet/R_OUT11: J27.14, U44.8
/CODEC interconnection sheet/R_OUT12: J27.26, U47.8
/CODEC interconnection sheet/R_OUT13: J27.48, U50.8
/CODEC interconnection sheet/R_OUT14: J27.60, U53.8
/CODEC interconnection sheet/R_OUT15: J27.72, U56.8
/CODEC interconnection sheet/SCL0: R70.1, U9.7, U10.13, U60.5
/CODEC interconnection sheet/SCL1: R74.1, U12.7, U13.13, U60.7
/CODEC interconnection sheet/SCL2: R78.1, U15.7, U16.13, U60.9
/CODEC interconnection sheet/SCL3: R82.1, U18.7, U19.13, U60.11
/CODEC interconnection sheet/SCL4: R86.1, U21.7, U22.13, U60.14
/CODEC interconnection sheet/SCL5: R90.1, U24.7, U25.13, U60.16
/CODEC interconnection sheet/SCL6: R94.1, U27.7, U28.13, U60.18
/CODEC interconnection sheet/SCL7: R98.1, U30.7, U31.13, U60.20
/CODEC interconnection sheet/SCL8: R71.1, U33.7, U34.13, U61.5
/CODEC interconnection sheet/SCL9: R75.1, U36.7, U37.13, U61.7
/CODEC interconnection sheet/SCL10: R79.1, U39.7, U40.13, U61.9
/CODEC interconnection sheet/SCL11: R83.1, U42.7, U43.13, U61.11
/CODEC interconnection sheet/SCL12: R87.1, U45.7, U46.13, U61.14
/CODEC interconnection sheet/SCL13: R91.1, U48.7, U49.13, U61.16
/CODEC interconnection sheet/SCL14: R95.1, U51.7, U52.13, U61.18
/CODEC interconnection sheet/SCL15: R99.1, U54.7, U55.13, U61.20
/CODEC interconnection sheet/SCL_HV0: J19.8, R15.2, U9.5, U9.6
/CODEC interconnection sheet/SCL_HV1: J19.20, R17.2, U12.5, U12.6
/CODEC interconnection sheet/SCL_HV2: J19.32, R19.2, U15.5, U15.6
/CODEC interconnection sheet/SCL_HV3: J19.54, R21.2, U18.5, U18.6
/CODEC interconnection sheet/SCL_HV4: J19.66, R23.2, U21.5, U21.6
/CODEC interconnection sheet/SCL_HV5: J19.78, R25.2, U24.5, U24.6
/CODEC interconnection sheet/SCL_HV10: J27.8, R35.2, U39.5, U39.6
/CODEC interconnection sheet/SCL_HV11: J27.20, R37.2, U42.5, U42.6
/CODEC interconnection sheet/SCL_HV12: J27.32, R39.2, U45.5, U45.6
/CODEC interconnection sheet/SCL_HV13: J27.54, R41.2, U48.5, U48.6
/CODEC interconnection sheet/SCL_HV14: J27.66, R43.2, U51.5, U51.6
/CODEC interconnection sheet/SCL_HV15: J27.78, R45.2, U54.5, U54.6
/CODEC interconnection sheet/SDA0: R68.1, U9.1, U10.14, U60.4
/CODEC interconnection sheet/SDA1: R72.1, U12.1, U13.14, U60.6
/CODEC interconnection sheet/SDA2: R76.1, U15.1, U16.14, U60.8
/CODEC interconnection sheet/SDA3: R80.1, U18.1, U19.14, U60.10
/CODEC interconnection sheet/SDA4: R84.1, U21.1, U22.14, U60.13
/CODEC interconnection sheet/SDA5: R88.1, U24.1, U25.14, U60.15
/CODEC interconnection sheet/SDA6: R92.1, U27.1, U28.14, U60.17
/CODEC interconnection sheet/SDA7: R96.1, U30.1, U31.14, U60.19
/CODEC interconnection sheet/SDA8: R69.1, U33.1, U34.14, U61.4
/CODEC interconnection sheet/SDA9: R73.1, U36.1, U37.14, U61.6
/CODEC interconnection sheet/SDA10: R77.1, U39.1, U40.14, U61.8
/CODEC interconnection sheet/SDA11: R81.1, U42.1, U43.14, U61.10
/CODEC interconnection sheet/SDA12: R85.1, U45.1, U46.14, U61.13
/CODEC interconnection sheet/SDA13: R89.1, U48.1, U49.14, U61.15
/CODEC interconnection sheet/SDA14: R93.1, U51.1, U52.14, U61.17
/CODEC interconnection sheet/SDA15: R97.1, U54.1, U55.14, U61.19
/CODEC interconnection sheet/SDA_HV0: J19.10, R16.2, U9.2, U9.3
/CODEC interconnection sheet/SDA_HV1: J19.22, R18.2, U12.2, U12.3
/CODEC interconnection sheet/SDA_HV2: J19.34, R20.2, U15.2, U15.3
/CODEC interconnection sheet/SDA_HV3: J19.56, R22.2, U18.2, U18.3
/CODEC interconnection sheet/SDA_HV4: J19.68, R24.2, U21.2, U21.3
/CODEC interconnection sheet/SDA_HV5: J19.80, R26.2, U24.2, U24.3
/CODEC interconnection sheet/SDA_HV10: J27.10, R36.2, U39.2, U39.3
/CODEC interconnection sheet/SDA_HV11: J27.22, R38.2, U42.2, U42.3
/CODEC interconnection sheet/SDA_HV12: J27.34, R40.2, U45.2, U45.3
/CODEC interconnection sheet/SDA_HV13: J27.56, R42.2, U48.2, U48.3
/CODEC interconnection sheet/SDA_HV14: J27.68, R44.2, U51.2, U51.3
/CODEC interconnection sheet/SDA_HV15: J27.80, R46.2, U54.2, U54.3
/CODEC interconnection sheet/WCLK0: U6.AB4, U10.7
/CODEC interconnection sheet/WCLK1: U6.AB8, U13.7
/CODEC interconnection sheet/WCLK2: U6.AB10, U16.7
/CODEC interconnection sheet/WCLK3: U6.AB14, U19.7
/CODEC interconnection sheet/WCLK4: U6.AB16, U22.7
/CODEC interconnection sheet/WCLK5: U6.AB19, U25.7
/CODEC interconnection sheet/WCLK6: U6.Y22, U28.7
/CODEC interconnection sheet/WCLK7: U6.U22, U31.7
/CODEC interconnection sheet/WCLK8: U6.G22, U34.7
/CODEC interconnection sheet/WCLK9: U6.D22, U37.7
/CODEC interconnection sheet/WCLK10: U6.A15, U40.7
/CODEC interconnection sheet/WCLK11: U6.A13, U43.7
/CODEC interconnection sheet/WCLK12: U6.A9, U46.7
/CODEC interconnection sheet/WCLK13: U6.A7, U49.7
/CODEC interconnection sheet/WCLK14: U6.A5, U52.7
/CODEC interconnection sheet/WCLK15: U6.A3, U55.7
/CODEC interconnection sheet/~RESET~0: U10.3, U59.1
/CODEC interconnection sheet/~RESET~1: U13.3, U59.2
/CODEC interconnection sheet/~RESET~2: U16.3, U59.3
/CODEC interconnection sheet/~RESET~3: U19.3, U59.4
/CODEC interconnection sheet/~RESET~4: U22.3, U59.5
/CODEC interconnection sheet/~RESET~5: U25.3, U59.6
/CODEC interconnection sheet/~RESET~6: U28.3, U59.7
/CODEC interconnection sheet/~RESET~7: U31.3, U59.8
/CODEC interconnection sheet/~RESET~8: U34.3, U59.10
/CODEC interconnection sheet/~RESET~9: U37.3, U59.11
/CODEC interconnection sheet/~RESET~10: U40.3, U59.12
/CODEC interconnection sheet/~RESET~11: U43.3, U59.13
/CODEC interconnection sheet/~RESET~12: U46.3, U59.14
/CODEC interconnection sheet/~RESET~13: U49.3, U59.15
/CODEC interconnection sheet/~RESET~14: U52.3, U59.16
/CODEC interconnection sheet/~RESET~15: U55.3, U59.17
/CODEC interconnection sheet/~RESET~I2C: R66.1, R67.1, U60.3, U61.3, U65.42
/CONF_DONE: R133.1, U6.M18, U65.10
/CRC_ERROR: R134.1, U6.L21, U65.11
/Clocking/+3V3C: C112.2, C113.2, C115.2, FB2.2, J1.1, R1.1, R6.1, R7.1, U7.3, U7.7, U7.14, U7.18, Y1.4
/Clocking/+3V3USB: Q2.C1, Q2.C2, Q2.C3
/Clocking/CLK_IN0: R2.1, U7.5
/Clocking/SCL: J1.2, R7.2, U7.10
/Clocking/SDA: J1.3, R6.2, U7.9
/Ethernet Connections/+3V3A: C416.2, C417.2, C418.2, C419.2, C420.2, C421.2, C422.2, FB21.1, R109.2, R111.2, R112.2, U62.4, U62.8, U62.11, U62.15, U62.17, U62.21
/Ethernet Connections/ACTLED: J4.1, U62.27
/Ethernet Connections/ETH_RX+: J4.14, R116.2, TR1.14
/Ethernet Connections/ETH_RX-: J4.17, R115.2, TR1.16
/Ethernet Connections/ETH_TX+: J4.12, TR1.9
/Ethernet Connections/ETH_TX-: J4.13, TR1.11
/Ethernet Connections/LINKLED: J4.10, U62.25
/Ethernet Connections/MISO: U62.34, U65.25
/Ethernet Connections/MOSI: U62.35, U65.26
/Ethernet Connections/NC_1+: J4.15, R119.2
/Ethernet Connections/NC_1-: J4.16, R120.2
/Ethernet Connections/NC_2+: J4.18, R121.2
/Ethernet Connections/NC_2-: J4.19, R122.2
/Ethernet Connections/~INT: U62.36, U65.24
/Ethernet Connections/~RESET: U62.37, U65.23
/Ethernet Connections/~SS: U62.32, U65.27
/FPGA Interconnects/DEV_ATT0: J19.9, U6.V6
/FPGA Interconnects/DEV_ATT1: J19.21, U6.V7
/FPGA Interconnects/DEV_ATT2: J19.33, U6.V8
/FPGA Interconnects/DEV_ATT3: J19.55, U6.V13
/FPGA Interconnects/DEV_ATT4: J19.67, U6.V14
/FPGA Interconnects/DEV_ATT5: J19.79, U6.V15
/FPGA Interconnects/DEV_ATT6: J11.9, U6.W21
/FPGA Interconnects/DEV_ATT7: J11.21, U6.T21
/FPGA Interconnects/DEV_ATT8: J11.67, U6.F21
/FPGA Interconnects/DEV_ATT9: J11.79, U6.C21
/FPGA Interconnects/DEV_ATT10: J27.9, U6.G15
/FPGA Interconnects/DEV_ATT11: J27.21, U6.G14
/FPGA Interconnects/DEV_ATT12: J27.33, U6.G10
/FPGA Interconnects/DEV_ATT13: J27.55, U6.G9
/FPGA Interconnects/DEV_ATT14: J27.67, U6.G8
/FPGA Interconnects/DEV_ATT15: J27.79, U6.G7
/FPGA Interconnects/DEV_INT0: J19.7, U6.W6
/FPGA Interconnects/DEV_INT1: J19.19, U6.W7
/FPGA Interconnects/DEV_INT2: J19.31, U6.W8
/FPGA Interconnects/DEV_INT3: J19.53, U6.W13
/FPGA Interconnects/DEV_INT4: J19.65, U6.W14
/FPGA Interconnects/DEV_INT5: J19.77, U6.W15
/FPGA Interconnects/DEV_INT6: J11.7, U6.W22
/FPGA Interconnects/DEV_INT7: J11.19, U6.T22
/FPGA Interconnects/DEV_INT8: J11.65, U6.F22
/FPGA Interconnects/DEV_INT9: J11.77, U6.C22
/FPGA Interconnects/DEV_INT10: J27.7, U6.F15
/FPGA Interconnects/DEV_INT11: J27.19, U6.F14
/FPGA Interconnects/DEV_INT12: J27.31, U6.F10
/FPGA Interconnects/DEV_INT13: J27.53, U6.F9
/FPGA Interconnects/DEV_INT14: J27.65, U6.F8
/FPGA Interconnects/DEV_INT15: J27.77, U6.F7
/FPGA Interconnects/MISO: R129.1, U6.K1
/FPGA Interconnects/MOSI: U6.D1, U68.5
/FPGA Interconnects/SCK: U6.K2, U68.6
/FPGA Interconnects/TCK: J30.1, R132.2, U6.L2
/FPGA Interconnects/TDI: J30.5, R136.1, U6.L5
/FPGA Interconnects/TDO: J30.2, U6.L4
/FPGA Interconnects/TMS: J30.3, R137.1, U6.L1
/FPGA Interconnects/~CONFIG: R131.1, U6.K5
/FPGA Interconnects/~CS: U6.E2, U68.1
/INIT_DONE: R135.1, U6.L22, U65.12
/Left Side Daughterboard Connector Interconnects/M_+12V: D43.1, D44.1, D45.1, D61.1, D62.1, D63.1, J12.12, J13.12, J14.12, J15.12, J16.12, J17.12, J18.37, J18.38, J18.39, J18.40, J18.41, J18.42, J18.43, J18.44
/Left Side Daughterboard Connector Interconnects/M_AUD_GND0: J12.1, J18.5
/Left Side Daughterboard Connector Interconnects/M_AUD_GND1: J13.1, J18.17
/Left Side Daughterboard Connector Interconnects/M_AUD_GND2: J14.1, J18.29
/Left Side Daughterboard Connector Interconnects/M_AUD_GND3: J15.1, J18.51
/Left Side Daughterboard Connector Interconnects/M_AUD_GND4: J16.1, J18.63
/Left Side Daughterboard Connector Interconnects/M_AUD_GND5: J17.1, J18.75
/Left Side Daughterboard Connector Interconnects/M_GND: D28.2, D29.2, D30.2, D31.2, D32.2, D33.2, D34.2, D35.2, D36.2, D37.2, D38.2, D39.2, D40.2, D41.2, D42.2, D43.2, D44.2, D45.2, D46.2, D47.2, D48.2, D49.2, D50.2, D51.2, D52.2, D53.2, D54.2, D55.2, D56.2, D57.2, D58.2, D59.2, D60.2, D61.2, D62.2, D63.2, J12.6, J12.10, J13.6, J13.10, J14.6, J14.10, J15.6, J15.10, J16.6, J16.10, J17.6, J17.10, J18.6, J18.11, J18.12, J18.18, J18.23, J18.24, J18.30, J18.35, J18.36, J18.45, J18.46, J18.52, J18.57, J18.58, J18.64, J18.69, J18.70, J18.76
/Left Side Daughterboard Connector Interconnects/M_ID_PIN0: D40.1, J12.11, J18.9
/Left Side Daughterboard Connector Interconnects/M_ID_PIN1: D41.1, J13.11, J18.21
/Left Side Daughterboard Connector Interconnects/M_ID_PIN2: D42.1, J14.11, J18.33
/Left Side Daughterboard Connector Interconnects/M_ID_PIN3: D58.1, J15.11, J18.55
/Left Side Daughterboard Connector Interconnects/M_ID_PIN4: D59.1, J16.11, J18.67
/Left Side Daughterboard Connector Interconnects/M_ID_PIN5: D60.1, J17.11, J18.79
/Left Side Daughterboard Connector Interconnects/M_INT_0: J12.9, J18.7
/Left Side Daughterboard Connector Interconnects/M_INT_1: J13.9, J18.19
/Left Side Daughterboard Connector Interconnects/M_INT_2: J14.9, J18.31
/Left Side Daughterboard Connector Interconnects/M_INT_3: J15.9, J18.53
/Left Side Daughterboard Connector Interconnects/M_INT_4: J16.9, J18.65
/Left Side Daughterboard Connector Interconnects/M_INT_5: J17.9, J18.77
/Left Side Daughterboard Connector Interconnects/M_L_IN0: C441.1, J18.3
/Left Side Daughterboard Connector Interconnects/M_L_IN1: C442.1, J18.15
/Left Side Daughterboard Connector Interconnects/M_L_IN2: C443.1, J18.27
/Left Side Daughterboard Connector Interconnects/M_L_IN3: C447.1, J18.49
/Left Side Daughterboard Connector Interconnects/M_L_IN4: C448.1, J18.61
/Left Side Daughterboard Connector Interconnects/M_L_IN5: C449.1, J18.73
/Left Side Daughterboard Connector Interconnects/M_L_OUT0: FB44.1, J18.2
/Left Side Daughterboard Connector Interconnects/M_L_OUT1: FB45.1, J18.16
/Left Side Daughterboard Connector Interconnects/M_L_OUT2: FB46.1, J18.28
/Left Side Daughterboard Connector Interconnects/M_L_OUT3: FB56.1, J18.50
/Left Side Daughterboard Connector Interconnects/M_L_OUT4: FB57.1, J18.62
/Left Side Daughterboard Connector Interconnects/M_L_OUT5: FB58.1, J18.74
/Left Side Daughterboard Connector Interconnects/M_R_IN0: C444.1, J18.1
/Left Side Daughterboard Connector Interconnects/M_R_IN1: C445.1, J18.13
/Left Side Daughterboard Connector Interconnects/M_R_IN2: C446.1, J18.25
/Left Side Daughterboard Connector Interconnects/M_R_IN3: C450.1, J18.47
/Left Side Daughterboard Connector Interconnects/M_R_IN4: C451.1, J18.59
/Left Side Daughterboard Connector Interconnects/M_R_IN5: C452.1, J18.71
/Left Side Daughterboard Connector Interconnects/M_R_OUT0: FB47.1, J18.4
/Left Side Daughterboard Connector Interconnects/M_R_OUT1: FB48.1, J18.14
/Left Side Daughterboard Connector Interconnects/M_R_OUT2: FB49.1, J18.26
/Left Side Daughterboard Connector Interconnects/M_R_OUT3: FB59.1, J18.48
/Left Side Daughterboard Connector Interconnects/M_R_OUT4: FB60.1, J18.60
/Left Side Daughterboard Connector Interconnects/M_R_OUT5: FB61.1, J18.72
/Left Side Daughterboard Connector Interconnects/M_SCL_HV0: J12.8, J18.8
/Left Side Daughterboard Connector Interconnects/M_SCL_HV1: J13.8, J18.20
/Left Side Daughterboard Connector Interconnects/M_SCL_HV2: J14.8, J18.32
/Left Side Daughterboard Connector Interconnects/M_SCL_HV3: J15.8, J18.54
/Left Side Daughterboard Connector Interconnects/M_SCL_HV4: J16.8, J18.66
/Left Side Daughterboard Connector Interconnects/M_SCL_HV5: J17.8, J18.78
/Left Side Daughterboard Connector Interconnects/M_SDA_HV0: J12.7, J18.10
/Left Side Daughterboard Connector Interconnects/M_SDA_HV1: J13.7, J18.22
/Left Side Daughterboard Connector Interconnects/M_SDA_HV2: J14.7, J18.34
/Left Side Daughterboard Connector Interconnects/M_SDA_HV3: J15.7, J18.56
/Left Side Daughterboard Connector Interconnects/M_SDA_HV4: J16.7, J18.68
/Left Side Daughterboard Connector Interconnects/M_SDA_HV5: J17.7, J18.80
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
